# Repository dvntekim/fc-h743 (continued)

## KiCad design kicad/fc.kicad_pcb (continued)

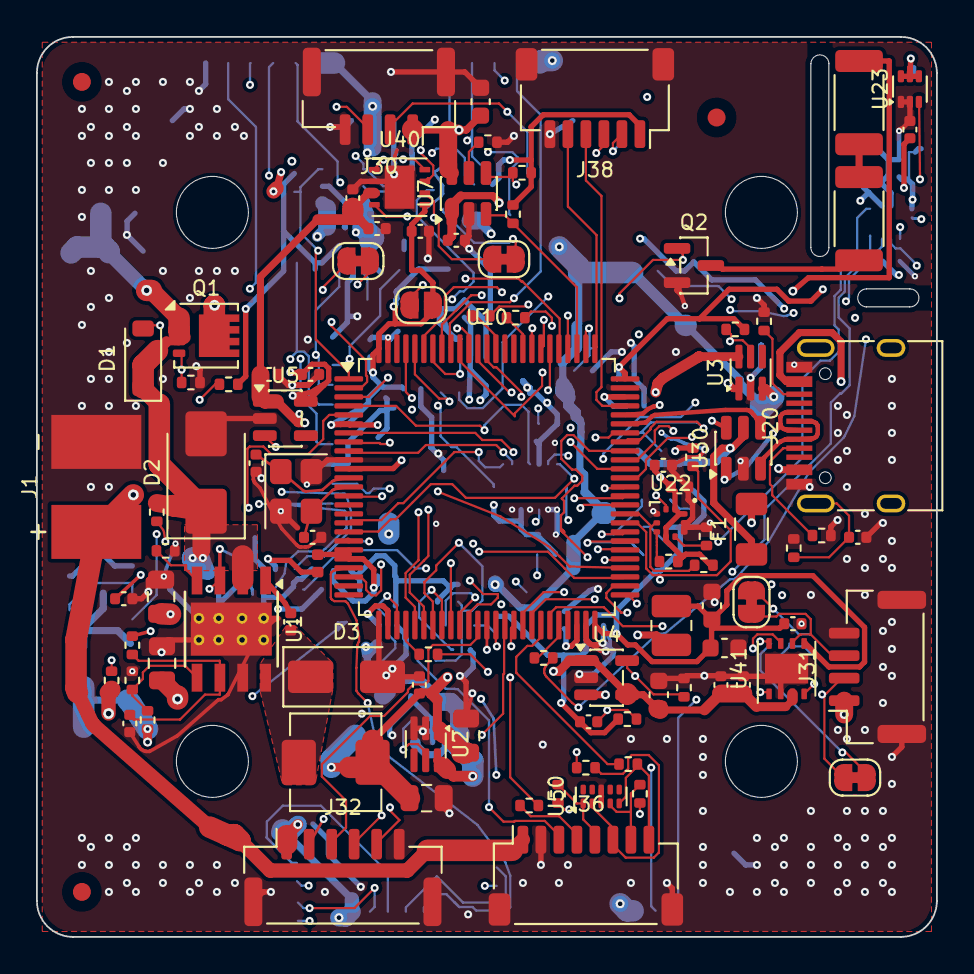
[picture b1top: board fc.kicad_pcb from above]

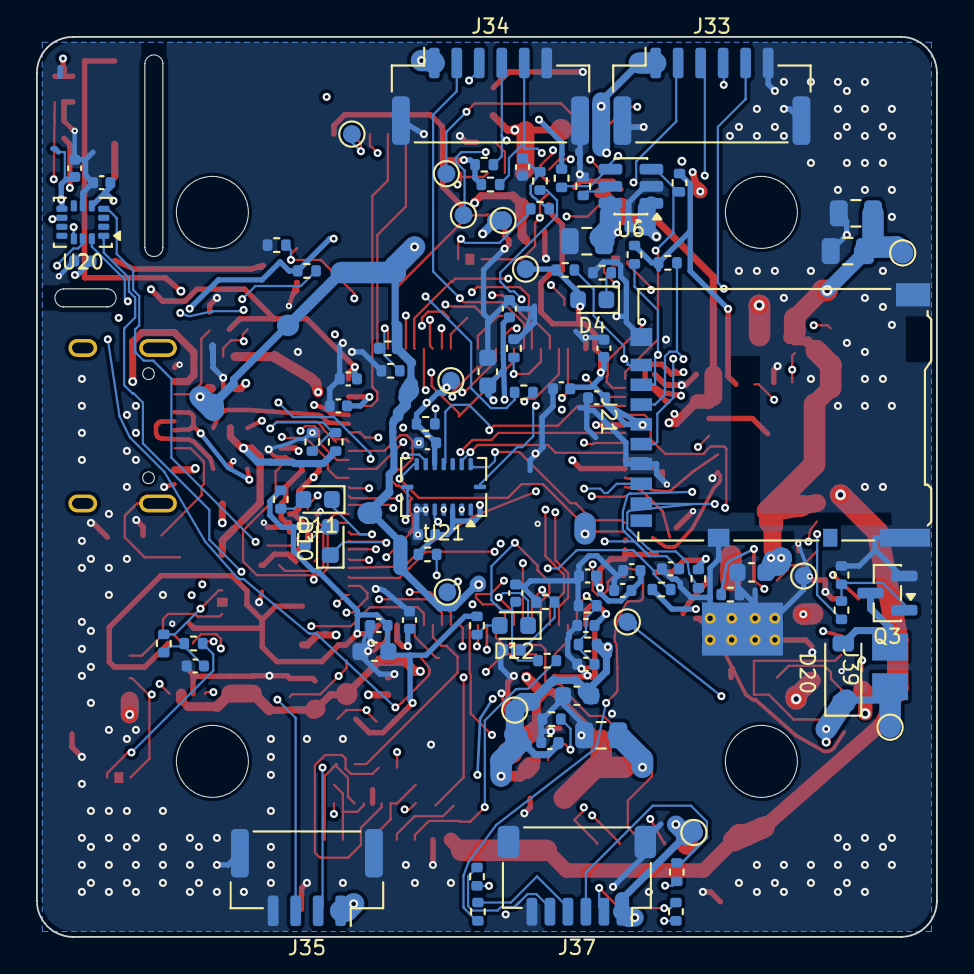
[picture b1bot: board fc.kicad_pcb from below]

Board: 6 copper layers, 50.0 x 50.0 mm, 203 parts (101 on the bottom side), 143 nets.

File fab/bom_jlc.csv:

Comment,Designator,Footprint,LCSC Part #
10uF,"C1,C2,C6,C7",C_0805_2012Metric,C440198
100nF,C3,C_0603_1608Metric,C14663
100nF,"C4,C5,C9,C13,C17,C18,C25,C27,C29,C30,C31,C32,C33,C34,C39,C40,C41,C44,C45,C47,C48,C49,C50,C53,C54,C56,C58,C60,C62",C_0402_1005Metric,C1525
22uF,"C10,C11,C12,C26",C_0805_2012Metric,C45783
4.7nF,"C14,C51,C57,C61",C_0402_1005Metric,C1538
47pF,C15,C_0402_1005Metric,C1567
10uF,"C16,C19,C21,C22,C28,C52",C_0603_1608Metric,C19702
10pF,C20,C_0402_1005Metric,C32949
1uF,"C23,C24,C38,C46,C55,C59",C_0402_1005Metric,C52923
4.7uF,C35,C_0603_1608Metric,C19666
2.2uF,"C36,C37",C_0402_1005Metric,C12530
12pF,"C42,C43",C_0402_1005Metric,C1547
BZT52C12,D1,D_SOD-123,C43491
SMBJ28A,D2,D_SMB,C113997
B360A-13-F,D3,D_SMA,C94193
GREEN PWR,D4,LED_0603_1608Metric,C2986059
RED,D10,LED_0603_1608Metric,C2286
BLUE,D11,LED_0603_1608Metric,C965807
GREEN,D12,LED_0603_1608Metric,C2986059
B5819W,D20,D_SOD-123,C8598
0.5A,F1,Fuse_1206_3216Metric,C69688
220R@100MHz,FB1,L_0402_1005Metric,C76885
USB-C,J20,USB_C_Receptacle_HRO_TYPE-C-31-M-12,C165948
microSD,J21,microSD_HC_Hirose_DM3AT-SF-PEJM5,C114218
CAN1,J30,JST_GH_SM04B-GHS-TB_1x04-1MP_P1.25mm_Horizontal,C189895
CAN2,J31,JST_GH_SM04B-GHS-TB_1x04-1MP_P1.25mm_Horizontal,C189895
TELEM1,J32,JST_GH_SM06B-GHS-TB_1x06-1MP_P1.25mm_Horizontal,C133065
TELEM2,J33,JST_GH_SM06B-GHS-TB_1x06-1MP_P1.25mm_Horizontal,C133065
GPS/I2C,J34,JST_GH_SM06B-GHS-TB_1x06-1MP_P1.25mm_Horizontal,C133065
RC,J35,JST_GH_SM04B-GHS-TB_1x04-1MP_P1.25mm_Horizontal,C189895
ESC,J36,JST_SH_SM08B-SRSS-TB_1x08-1MP_P1.00mm_Horizontal,C160407
AUX,J37,JST_SH_SM06B-SRSS-TB_1x06-1MP_P1.00mm_Horizontal,C56123098
DEBUG,J38,JST_SH_SM06B-SRSS-TB_1x06-1MP_P1.00mm_Horizontal,C56123098
4.7uH,L1,L_Changjiang_FXL0530,C177246
2.2uH,L2,L_1008_2520Metric,C98350
DMP4013LFGQ-13,Q1,Diodes_PowerDI3333-8,C7264680
AO3400A,Q2,SOT-23,C20917
2N7002,Q3,SOT-23,C8545
100k,"R1,R2,R11,R18,R19,R21,R24,R43,R74",R_0402_1005Metric,C25741
10k,"R3,R9,R12,R13,R14,R15,R16,R22,R25,R27,R35,R36,R37,R38,R39",R_0402_1005Metric,C25744
1k,"R4,R32,R68",R_0402_1005Metric,C11702
147k,R5,R_0402_1005Metric,C64171
36k,R6,R_0402_1005Metric,C43676
162k,R7,R_0402_1005Metric,C54068
53.6k,R8,R_0402_1005Metric,C53398
9.09k,R10,R_0402_1005Metric,C11549
453k,R17,R_0402_1005Metric,C27009
20k,R20,R_0402_1005Metric,C25765
22k,"R23,R51",R_0402_1005Metric,C25768
2k,R26,R_0402_1005Metric,C4109
33,"R28,R29,R31",R_0402_1005Metric,C25105
22,R30,R_0402_1005Metric,C25092
470,"R33,R34",R_0402_1005Metric,C25117
2.2k,"R40,R41,R62,R63",R_0402_1005Metric,C25879
4.7k,R42,R_0402_1005Metric,C25900
12,"R44,R45",R_2010_5025Metric,C3013299
5.1k,"R48,R49",R_0402_1005Metric,C25905
1M,R50,R_0402_1005Metric,C26083
33k,R52,R_0402_1005Metric,C25779
47k,"R53,R54,R55,R56,R57",R_0402_1005Metric,C25792
60.4,"R58,R59,R60,R61",R_0402_1005Metric,C60310
47,"R64,R65,R66,R67,R69,R70,R71,R72",R_0402_1005Metric,C25118
100,R73,R_0402_1005Metric,C25076
TPS54360BDDAR,U1,TI_SO-PowerPAD-8_ThermalVias,C524806
LM66100DCKR,"U2,U3",SOT-363_SC-70-6,C2869734
TLV62569DBVR,U4,SOT-23-5,C141836
LP5907MFX-3.3/NOPB,U5,SOT-23-5,C80670
TPS2553DBVR,"U6,U7",SOT-23-6,C55266
STM32H743VIT6,U10,LQFP-100_14x14mm_P0.5mm,C114409
ICM-45686,U20,LGA-14_3x2.5mm_P0.5mm_LayoutBorder3x4y,C22459454
BMI088,U21,Bosch_LGA-16_4.5x3mm_P0.5mm_LayoutBorder7x1y_ClockwisePinNumbering,C194919
BMP581,U22,Bosch_LGA-10_2x2mm_P0.5mm_BMP581,C5362283
TMP302ADRLR,U23,SOT-563,C2877557
USBLC6-2SC6,U30,SOT-23-6,C7519
TCAN1462VDRBRQ1,"U40,U41",TI_DRB0008J_VSON-8_3x3mm_P0.65mm,C5215833
TPD4E05U06DQAR,U50,USON-10_2.5x1.0mm_P0.5mm,C138714
16MHz,Y1,Crystal_SMD_3225-4Pin_3.2x2.5mm,C13738

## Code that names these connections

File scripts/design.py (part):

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R("10k", "USB_PWR_SEL", "+3V3", S, note="ST high = board running from USB")
C("10uF", "+5V_FMU", "GND", S)
C("100nF", "+5V_FMU", "GND", S)
R("10k", "+5V", "MAIN_5V_DET", S, note="buck-present detect for PX4 (PA15)")
R("10k", "MAIN_5V_DET", "GND", S)
R("10k", "+5V_FMU", "V5_SENSE", S, note="scaled 5 V for PX4 ADC (PA4), /2")
R("10k", "V5_SENSE", "GND", S)
C("100nF", "V5_SENSE", "GND", S)

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S = "mcu"
MCU_PINS = {  # port -> net. Follows FMUv6C unless noted in PINMAP_NOTES
    # SPI1: ICM-45686
    "PA5": "SPI1_SCK_MCU", "PA6": "SPI1_MISO", "PA7": "SPI1_MOSI", "PC13": "IMU1_CS", "PE6": "IMU1_DRDY",
    # SPI2: BMI088
    "PD3": "SPI2_SCK_MCU", "PC2_C": "SPI2_MISO", "PC3_C": "SPI2_MOSI",
    "PC14": "BMI_GYRO_CS", "PC15": "BMI_ACC_CS", "PE5": "BMI_GYRO_DRDY", "PE4": "BMI_ACC_DRDY",
    "PB10": "IMU_CLKIN_MCU",
    # I2C
    "PD12": "I2C4_SCL", "PD13": "I2C4_SDA", "PB8": "I2C1_SCL", "PB7": "I2C1_SDA",
    # UARTs
    "PE8": "TELEM1_TX", "PE7": "TELEM1_RX", "PE9": "TELEM1_RTS", "PE10": "TELEM1_CTS",
    "PC12": "TELEM2_TX", "PD2": "TELEM2_RX", "PC8": "TELEM2_RTS", "PC9": "TELEM2_CTS",
    "PB6": "GPS_TX", "PA10": "GPS_RX",
    "PC6": "RC_TX", "PC7": "RC_RX",
    "PE0": "ESC_TLM_MCU",
    "PD8": "CONSOLE_TX", "PD9": "CONSOLE_RX",
    # CAN
    "PD1": "CAN1_TX", "PD0": "CAN1_RX", "PE12": "CAN1_STB",
    "PB13": "CAN2_TX", "PB5": "CAN2_RX", "PB12": "CAN2_STB",
    # SDMMC2
    "PD6": "SD_CLK_MCU", "PD7": "SD_CMD", "PB14": "SD_D0", "PB15": "SD_D1", "PB3": "SD_D2", "PB4": "SD_D3",
    # USB
    "PA11": "USB_DM", "PA12": "USB_DP", "PA9": "VBUS_SENSE",
    # motors (TIM1 = BDShot group, as FMUv6C)
    "PA8": "M1_MCU", "PE11": "M2_MCU", "PE13": "M3_MCU", "PE14": "M4_MCU",
    "PD14": "M5_MCU", "PD15": "M6_MCU", "PA0": "M7_MCU", "PA1": "M8_MCU",
    # ADC
    "PC5": "VBAT_SENSE", "PC4": "BATT_CURR_SENSE", "PA4": "V5_SENSE",
    # power control / status
    "PB2": "SENS_EN", "PE2": "PERIPH_EN", "PE3": "PERIPH_nOC", "PC10": "CAN5V_EN", "PC11": "CAN5V_nOC",
    "PA15": "MAIN_5V_DET", "PE15": "USB_PWR_SEL",
    "PB9": "HEATER_PWM", "PB0": "BUZZER",
    "PD10": "LED_R_N", "PD11": "LED_B_N", "PB1": "LED_G_N",
    # debug
    "PA13": "SWDIO", "PA14": "SWCLK",
    # clocks / system
    "PH0": "HSE_IN", "PH1": "HSE_OUT", "NRST": "NRST", "BOOT0": "BOOT0",
    "VBAT": "+3V3", "VDD": "+3V3", "VSS": "GND", "VSSA": "GND", "VDDA": "VDDA", "VREF+": "VDDA",
}
PINMAP_NOTES = [
    "BMI088 moved from SPI1 (FMUv6C) to SPI2 (PD3/PC2_C/PC3_C, FMUv6C's FRAM bus): each IMU on its own bus.",
    "No FRAM: PX4 parameters live on the microSD card.",
    "PB10 (FMUv6C I2C2_SCL) repurposed as TIM2_CH3 32 kHz IMU clock to ICM-45686 CLKIN (ARK Pi6X pattern).",
    "PE12 (FMUv6C HW_VER drive) -> CAN1 STB; PB12 (FMUv6C nPOWER_IN_B) -> CAN2 STB.",
    "PE0 UART8_RX -> ESC telemetry (FMUv6C GPS2). USART6 (FMUv6C PX4IO) -> RC receiver.",
    "PA15 -> buck-present detect; PE15 -> USB power-path status (LM66100 ST).",
    "PB1 (FMUv6C BATT2 voltage) -> green status LED.",
    "PC10/PC11 (FMUv6C 5V_HIPOWER EN/nOC) -> CAN connector power switch EN/nOC (active-high EN on TPS2553).",
]
group("STM32H743VIT6")
pins_db = json.load(open(os.path.join(HERE, "h743_pins.json")))
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part("U20", "fc_custom:ICM-45686", "ICM-45686", "Package_LGA:LGA-14_3x2.5mm_P0.5mm_LayoutBorder3x4y",
     "C22459454", S, {1: "SPI1_MISO", 2: None, 3: None, 4: "IMU1_DRDY", 5: "+3V3_SENS", 6: "GND", 7: None,
                      8: "+3V3_SENS", 9: "IMU_CLKIN", 10: None, 11: None, 12: "IMU1_CS", 13: "SPI1_SCK",
                      14: "SPI1_MOSI"}, note="primary IMU, SPI1, CLKIN on pin 9")
C("100nF", "+3V3_SENS", "GND", S, note="U20 VDD")
C("100nF", "+3V3_SENS", "GND", S, note="U20 VDDIO")
C("1uF", "+3V3_SENS", "GND", S, note="U20 bulk")
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
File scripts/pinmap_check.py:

"""CubeMX-style pin-map check.

For every MCU pin the design uses, state the peripheral function it must
provide and confirm that function is in ST's alternate-function list for that
pin (taken from the KiCad STM32H743VITx symbol, generated from ST's pin
database). Also checks no function is claimed twice and that PX4's FMUv6C
assignments are kept where the design says they are.
"""
import json, sys
from design import MCU_PINS, PINMAP_NOTES

REQ = {  # pin -> required alternate function (None = plain GPIO / EXTI)
    "PA5": "SPI1_SCK", "PA6": "SPI1_MISO", "PA7": "SPI1_MOSI", "PC13": None, "PE6": None,
    "PD3": "SPI2_SCK", "PC2_C": "SPI2_MISO", "PC3_C": "SPI2_MOSI", "PC14": None, "PC15": None,
    "PE5": None, "PE4": None, "PB10": "TIM2_CH3",
    "PD12": "I2C4_SCL", "PD13": "I2C4_SDA", "PB8": "I2C1_SCL", "PB7": "I2C1_SDA",
    "PE8": "UART7_TX", "PE7": "UART7_RX", "PE9": "UART7_RTS", "PE10": "UART7_CTS",
    "PC12": "UART5_TX", "PD2": "UART5_RX", "PC8": "UART5_RTS", "PC9": "UART5_CTS",
    "PB6": "USART1_TX", "PA10": "USART1_RX", "PC6": "USART6_TX", "PC7": "USART6_RX",
    "PE0": "UART8_RX", "PD8": "USART3_TX", "PD9": "USART3_RX",
    "PD1": "FDCAN1_TX", "PD0": "FDCAN1_RX", "PB13": "FDCAN2_TX", "PB5": "FDCAN2_RX",
    "PE12": None, "PB12": None,
    "PD6": "SDMMC2_CK", "PD7": "SDMMC2_CMD", "PB14": "SDMMC2_D0", "PB15": "SDMMC2_D1",
    "PB3": "SDMMC2_D2", "PB4": "SDMMC2_D3",
    "PA11": "USB_OTG_FS_DM", "PA12": "USB_OTG_FS_DP", "PA9": None,
    "PA8": "TIM1_CH1", "PE11": "TIM1_CH2", "PE13": "TIM1_CH3", "PE14": "TIM1_CH4",
    "PD14": "TIM4_CH3", "PD15": "TIM4_CH4", "PA0": "TIM5_CH1", "PA1": "TIM5_CH2",
    "PC5": "ADC1_INP8", "PC4": "ADC1_INP4", "PA4": "ADC1_INP18",
    "PB9": "TIM17_CH1", "PB0": "TIM3_CH3",
    "PA13": "DEBUG_JTMS-SWDIO", "PA14": "DEBUG_JTCK-SWCLK",
    "PH0": "RCC_OSC_IN", "PH1": "RCC_OSC_OUT",
}
# FMUv6C assignments (boards/px4/fmu-v6c board.h / board_config.h / timer_config.cpp / spi.cpp)
FMUV6C = {
    "PA5": "SPI1_SCK", "PA6": "SPI1_MISO", "PA7": "SPI1_MOSI", "PC13": "ICM42688P CS", "PE6": "ICM42688P DRDY",
    "PC14": "BMI088 gyro CS", "PC15": "BMI088 accel CS", "PE5": "BMI088 gyro DRDY", "PE4": "BMI088 accel DRDY",
    "PD3": "SPI2_SCK", "PC2_C": "SPI2_MISO", "PC3_C": "SPI2_MOSI",
    "PD12": "I2C4_SCL", "PD13": "I2C4_SDA", "PB8": "I2C1_SCL", "PB7": "I2C1_SDA",
    "PE8": "UART7_TX", "PE7": "UART7_RX", "PE9": "UART7_RTS", "PE10": "UART7_CTS",
    "PC12": "UART5_TX", "PD2": "UART5_RX", "PC9": "UART5_CTS", "PB6": "USART1_TX", "PA10": "USART1_RX",
    "PC6": "USART6_TX", "PC7": "USART6_RX", "PE0": "UART8_RX", "PD8": "USART3_TX", "PD9": "USART3_RX",
    "PD1": "FDCAN1_TX", "PD0": "FDCAN1_RX", "PB13": "FDCAN2_TX", "PB5": "FDCAN2_RX",
    "PD6": "SDMMC2_CK", "PD7": "SDMMC2_CMD", "PB3": "SDMMC2_D2",
    "PA8": "TIM1_CH1", "PE11": "TIM1_CH2", "PE13": "TIM1_CH3", "PE14": "TIM1_CH4",
    "PD14": "TIM4_CH3", "PD15": "TIM4_CH4", "PA0": "TIM5_CH1", "PA1": "TIM5_CH2",
    "PC5": "ADC BATT1 V", "PC4": "ADC BATT1 I", "PA4": "ADC scaled 5V", "PB9": "heater TIM17_CH1",
    "PB0": "buzzer TIM3_CH3", "PB2": "3V3 sensors EN", "PE2": "5V periph EN", "PE3": "5V periph OC",
    "PC10": "5V hipower EN", "PC11": "5V hipower OC", "PD10": "LED red", "PD11": "LED blue", "PA9": "OTG VBUS",
    "PA15": "brick1 valid", "PE15": "USB valid",
}


def main():
    pins = {p[1]: (p[0], set(p[3])) for p in json.load(open("h743_pins.json"))}
    rows, errors = [], []
    seen = {}
    for name, net in sorted(MCU_PINS.items(), key=lambda kv: kv[0]):
        if name not in pins or name in ("VDD", "VSS", "VBAT", "VDDA", "VSSA", "VREF+", "NRST", "BOOT0"):
            continue
        num, alts = pins[name]
        req = REQ.get(name, "GPIO" if name.startswith("P") else None)
        ok = req in (None, "GPIO") or req in alts
        if not ok:
            errors.append(f"{name}: needs {req}, not in {sorted(alts)}")
        if req not in (None, "GPIO"):
            if req in seen:
                errors.append(f"{req} claimed by {seen[req]} and {name}")
            seen[req] = name
        v6c = FMUV6C.get(name, "-")
        rows.append((num, name, net, req or "GPIO", "OK" if ok else "FAIL", v6c))
    # timers: channels used per timer
    tim = {}
    for _, name, net, req, _, _ in rows:
        if req and req.startswith("TIM"):
            t = req.split("_")[0]
            tim.setdefault(t, []).append(f"{req.split('_')[1]}={name}({net})")
    with open("pinmap.md", "w") as f:
        f.write("# Pin map check (STM32H743VIT6, LQFP-100)\n\n")
        f.write("Alternate functions are checked against ST's pin data as shipped in the KiCad "
                "`MCU_ST_STM32H7:STM32H743VITx` symbol. `FMUv6C` shows what PX4's Pixhawk 6C target "
                "uses the same pin for.\n\n")
        f.write("| Pin | Port | Net | Function needed | AF check | FMUv6C use |\n|---|---|---|---|---|---|\n")
        for r in sorted(rows):
            f.write("| %s | %s | %s | %s | %s | %s |\n" % r)
        f.write("\n## Timers\n\n")
        for t, ch in sorted(tim.items()):
            f.write(f"- {t}: {', '.join(ch)}\n")
        f.write("\nTIM8 is PX4's HRT on FMUv6C (no pins). TIM2 only drives the 32 kHz IMU clock.\n")
        f.write("\n## Deviations from FMUv6C\n\n")
        for n in PINMAP_NOTES:
            f.write(f"- {n}\n")
        f.write("\n## Result\n\n")
        f.write("PASS: no conflicts\n" if not errors else "FAIL:\n" + "\n".join(f"- {e}" for e in errors) + "\n")
    print("errors:", errors or "none", "| pins used:", len(rows))
    return 1 if errors else 0


if __name__ == "__main__":
    sys.exit(main())
